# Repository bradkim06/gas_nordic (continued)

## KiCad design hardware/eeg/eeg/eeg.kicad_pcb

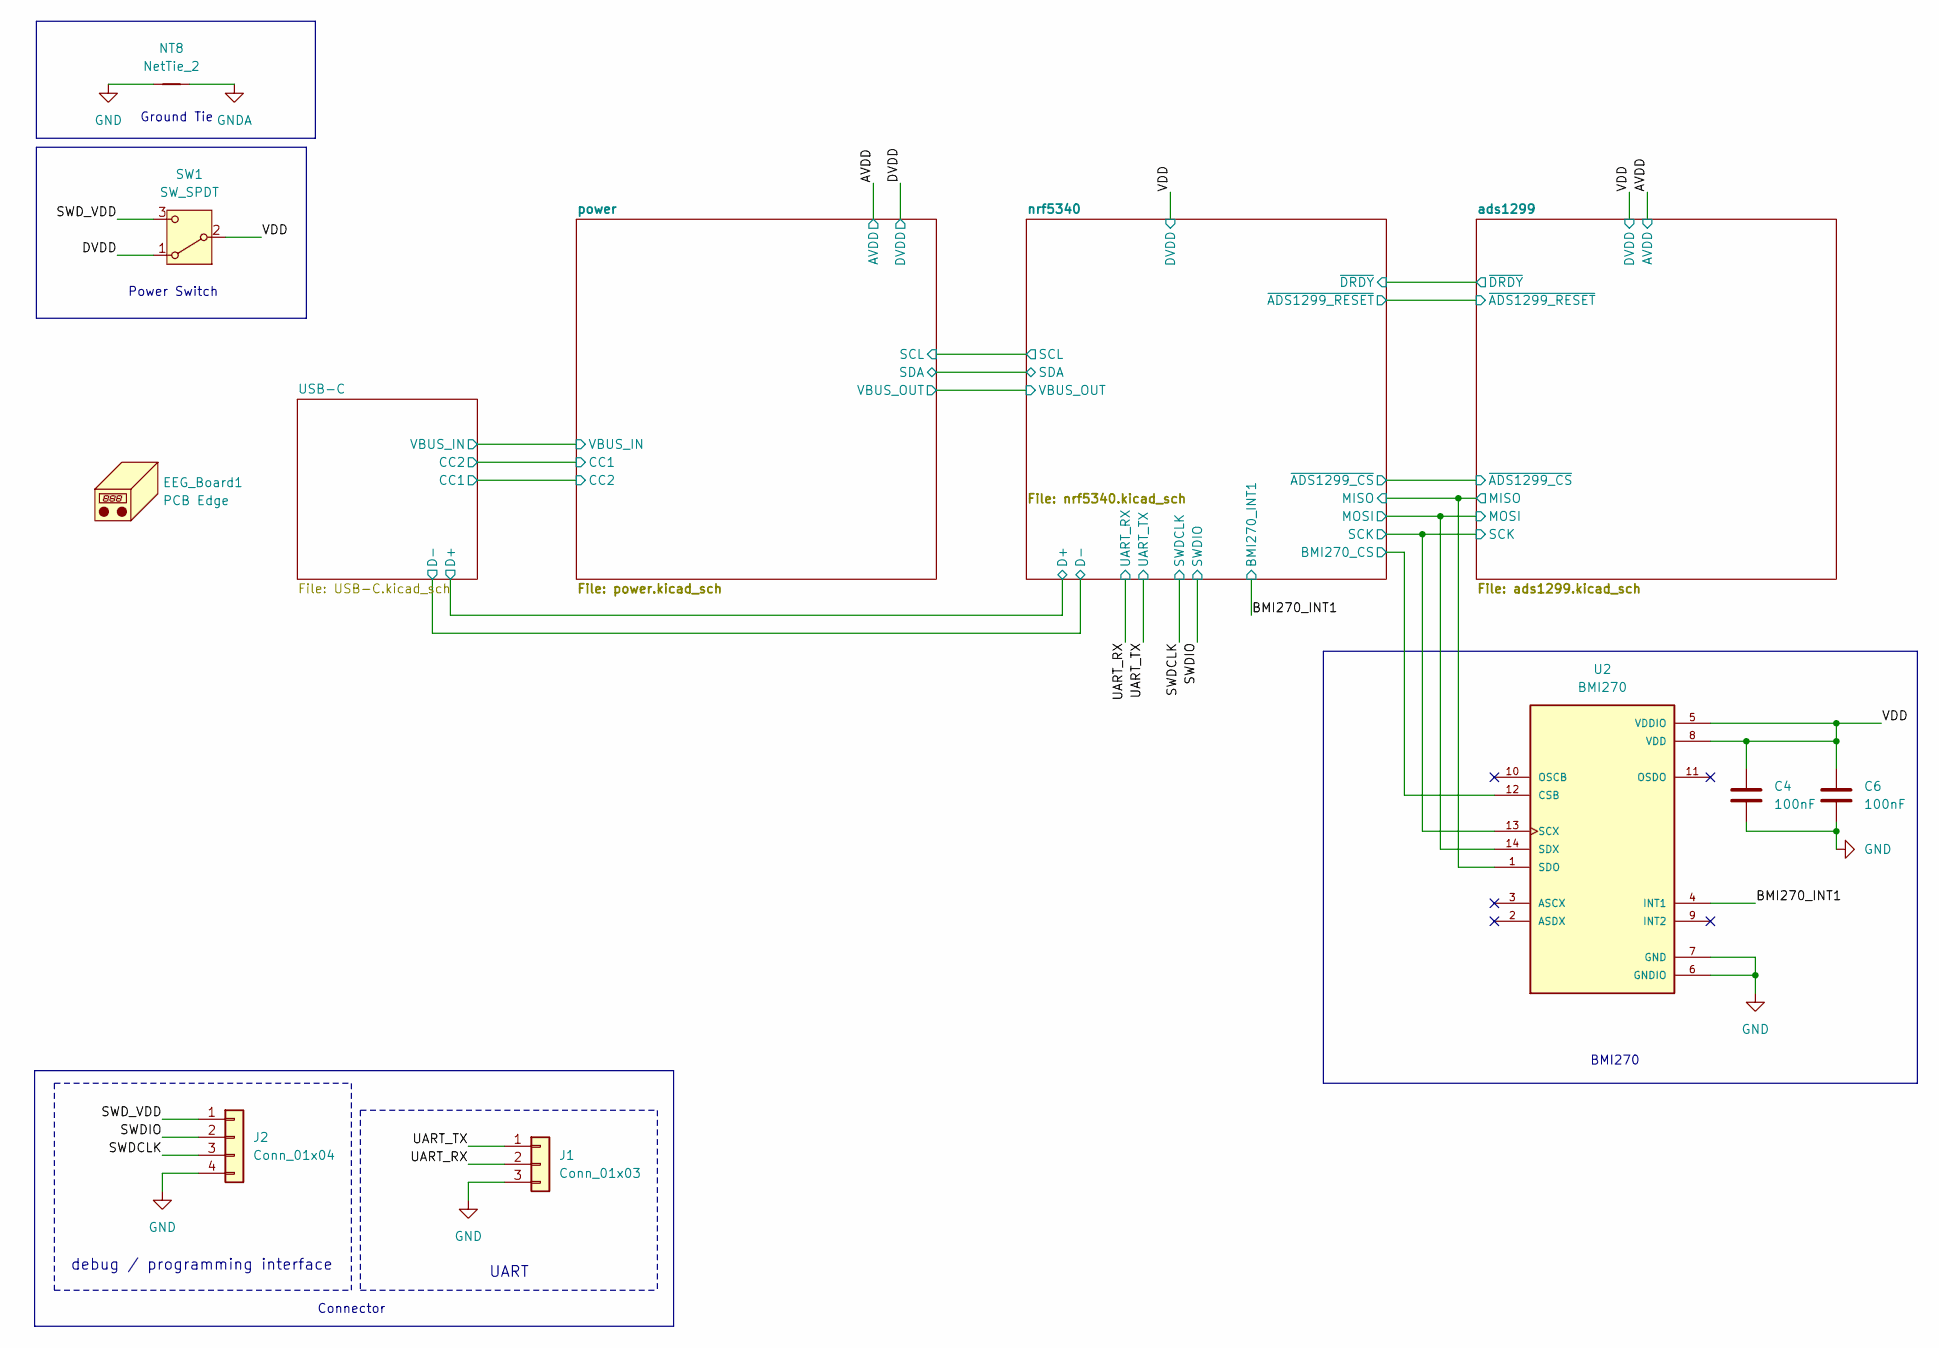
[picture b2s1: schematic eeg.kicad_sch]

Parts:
C4, C6: 100nF; C_0402_1005Metric; MANUFACTURER_PART_NUMBER GRM155R71C104KA88D
EEG_Board1: PCB Edge; eeg
J1: Conn_01x03; PinHeader_1x03_P1.27mm_Vertical; MANUFACTURER_PART_NUMBER 1.25T-3A
J2: Conn_01x04; PinHeader_1x04_P1.27mm_Vertical; MANUFACTURER_PART_NUMBER 1.25T-4A
NT8: NetTie_2; NetTie-2_SMD_Pad0.5mm
SW1: SW_SPDT; SK12D07VG4NSPA_CNK; MANUFACTURER_PART_NUMBER SK12D07VG5
U2: BMI270; XDCR_BMI270; MANUFACTURER_PART_NUMBER BMI270

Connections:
/BMI270_INT1: U2.4 (INT1); also elsewhere on the board
/DVDD: SW1.1 (A); also elsewhere on the board
/SWDCLK: J2.3; also elsewhere on the board
/SWDIO: J2.2; also elsewhere on the board
/SWD_VDD: J2.1, SW1.3 (C)
/UART_RX: J1.2; also elsewhere on the board
/UART_TX: J1.1; also elsewhere on the board
/VDD: C4.1, C6.1, SW1.2 (B), U2.5 (VDDIO), U2.8 (VDD); also elsewhere on the board
/ads1299/MISO: U2.1 (SDO); also elsewhere on the board
/ads1299/MOSI: U2.14 (SDX); also elsewhere on the board
/ads1299/SCK: U2.13 (SCX); also elsewhere on the board
/nrf5340/BMI270_CS: U2.12 (CSB); also elsewhere on the board
GND: C4.2, C6.2, J1.3, J2.4, NT8.1, U2.6 (GNDIO), U2.7 (GND); also elsewhere on the board
GNDA: NT8.2; also elsewhere on the board

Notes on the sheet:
Ground Tie
UART
Connector
BMI270
Power Switch
debug / programming interface

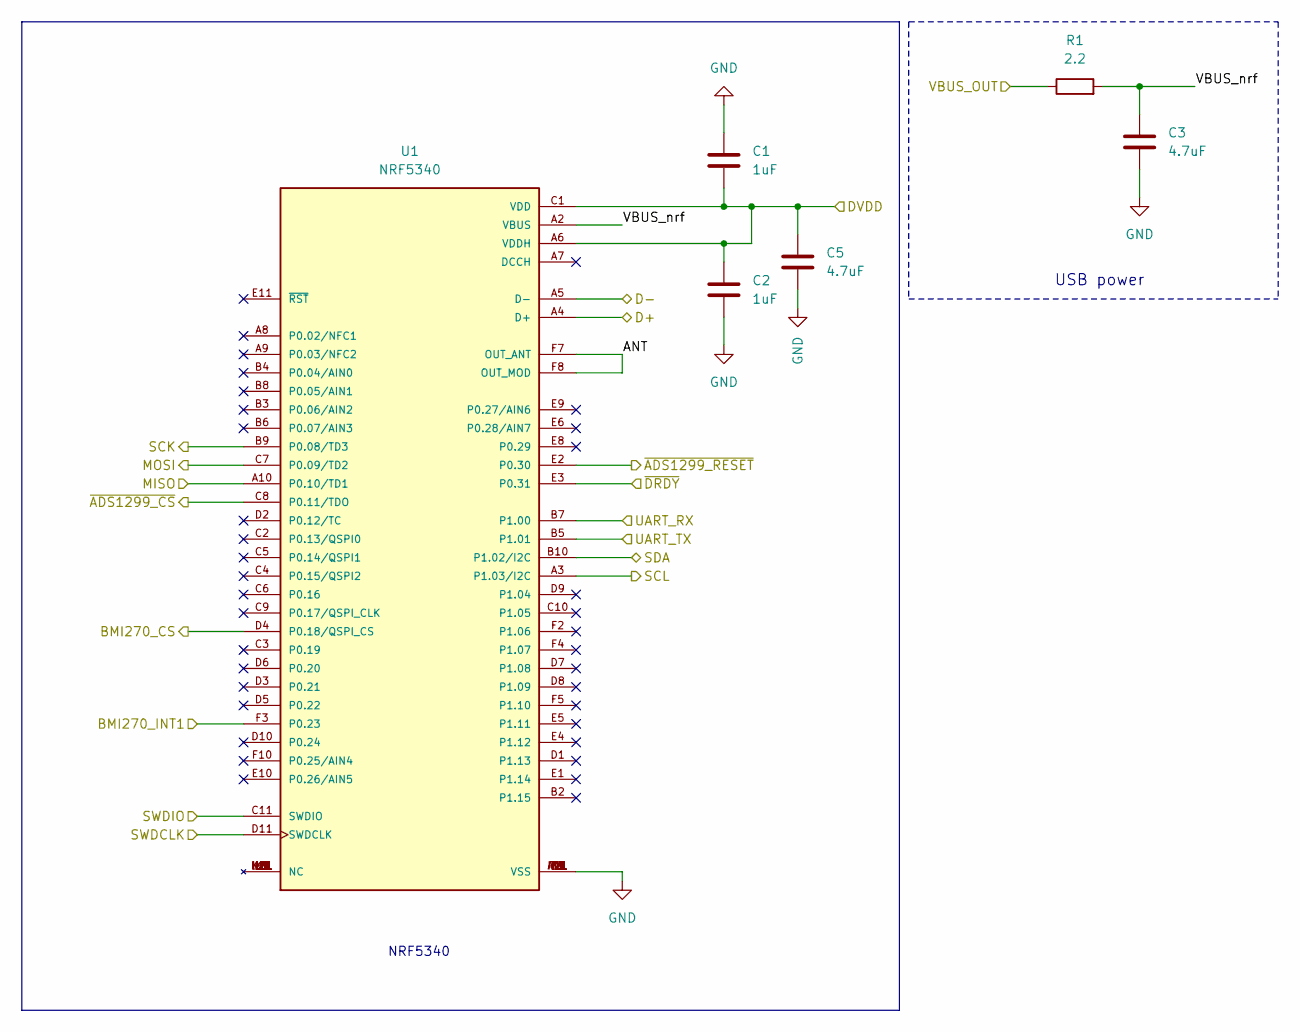
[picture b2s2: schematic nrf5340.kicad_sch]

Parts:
C1, C2: 1uF; C_0402_1005Metric; MANUFACTURER_PART_NUMBER GRM155R61A105KE15D
C3, C5: 4.7uF; C_0402_1005Metric; MANUFACTURER_PART_NUMBER GRM155R61A475MEAAD
R1: 2.2; R_0402_1005Metric; MANUFACTURER_PART_NUMBER RC0402FR-072R2L
U1: NRF5340; XCVR_ISP2053-AX-RS; PARTREV R6

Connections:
/BMI270_INT1: U1.F3 (P0.23); also elsewhere on the board
/SWDCLK: U1.D11 (SWDCLK); also elsewhere on the board
/SWDIO: U1.C11 (SWDIO); also elsewhere on the board
/UART_RX: U1.B7 (P1.00); also elsewhere on the board
/UART_TX: U1.B5 (P1.01); also elsewhere on the board
/USB-C/D+: U1.A4 (D+); also elsewhere on the board
/USB-C/D-: U1.A5 (D-); also elsewhere on the board
/VDD: C1.2, C2.1, C5.1, U1.A6 (VDDH), U1.C1 (VDD); also elsewhere on the board
/ads1299/MISO: U1.A10 (P0.10/TD1); also elsewhere on the board
/ads1299/MOSI: U1.C7 (P0.09/TD2); also elsewhere on the board
/ads1299/SCK: U1.B9 (P0.08/TD3); also elsewhere on the board
/ads1299/~ADS1299_CS: U1.C8 (P0.11/TDO); also elsewhere on the board
/ads1299/~ADS1299_RESET: U1.E2 (P0.30); also elsewhere on the board
/ads1299/~DRDY: U1.E3 (P0.31); also elsewhere on the board
/nrf5340/ANT: U1.F7 (OUT_ANT), U1.F8 (OUT_MOD)
/nrf5340/BMI270_CS: U1.D4 (P0.18/QSPI_CS); also elsewhere on the board
/nrf5340/SCL: U1.A3 (P1.03/I2C); also elsewhere on the board
/nrf5340/SDA: U1.B10 (P1.02/I2C); also elsewhere on the board
/nrf5340/VBUS_OUT: R1.1; also elsewhere on the board
/nrf5340/VBUS_nrf: C3.1, R1.2, U1.A2 (VBUS)
GND: C1.1, C2.2, C3.2, C5.2, U1.A1 (VSS), U1.A11 (VSS), U1.E7 (VSS), U1.F1 (VSS), U1.F6 (VSS), U1.F9 (VSS), U1.F11 (VSS); also elsewhere on the board

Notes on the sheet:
NRF5340
USB power

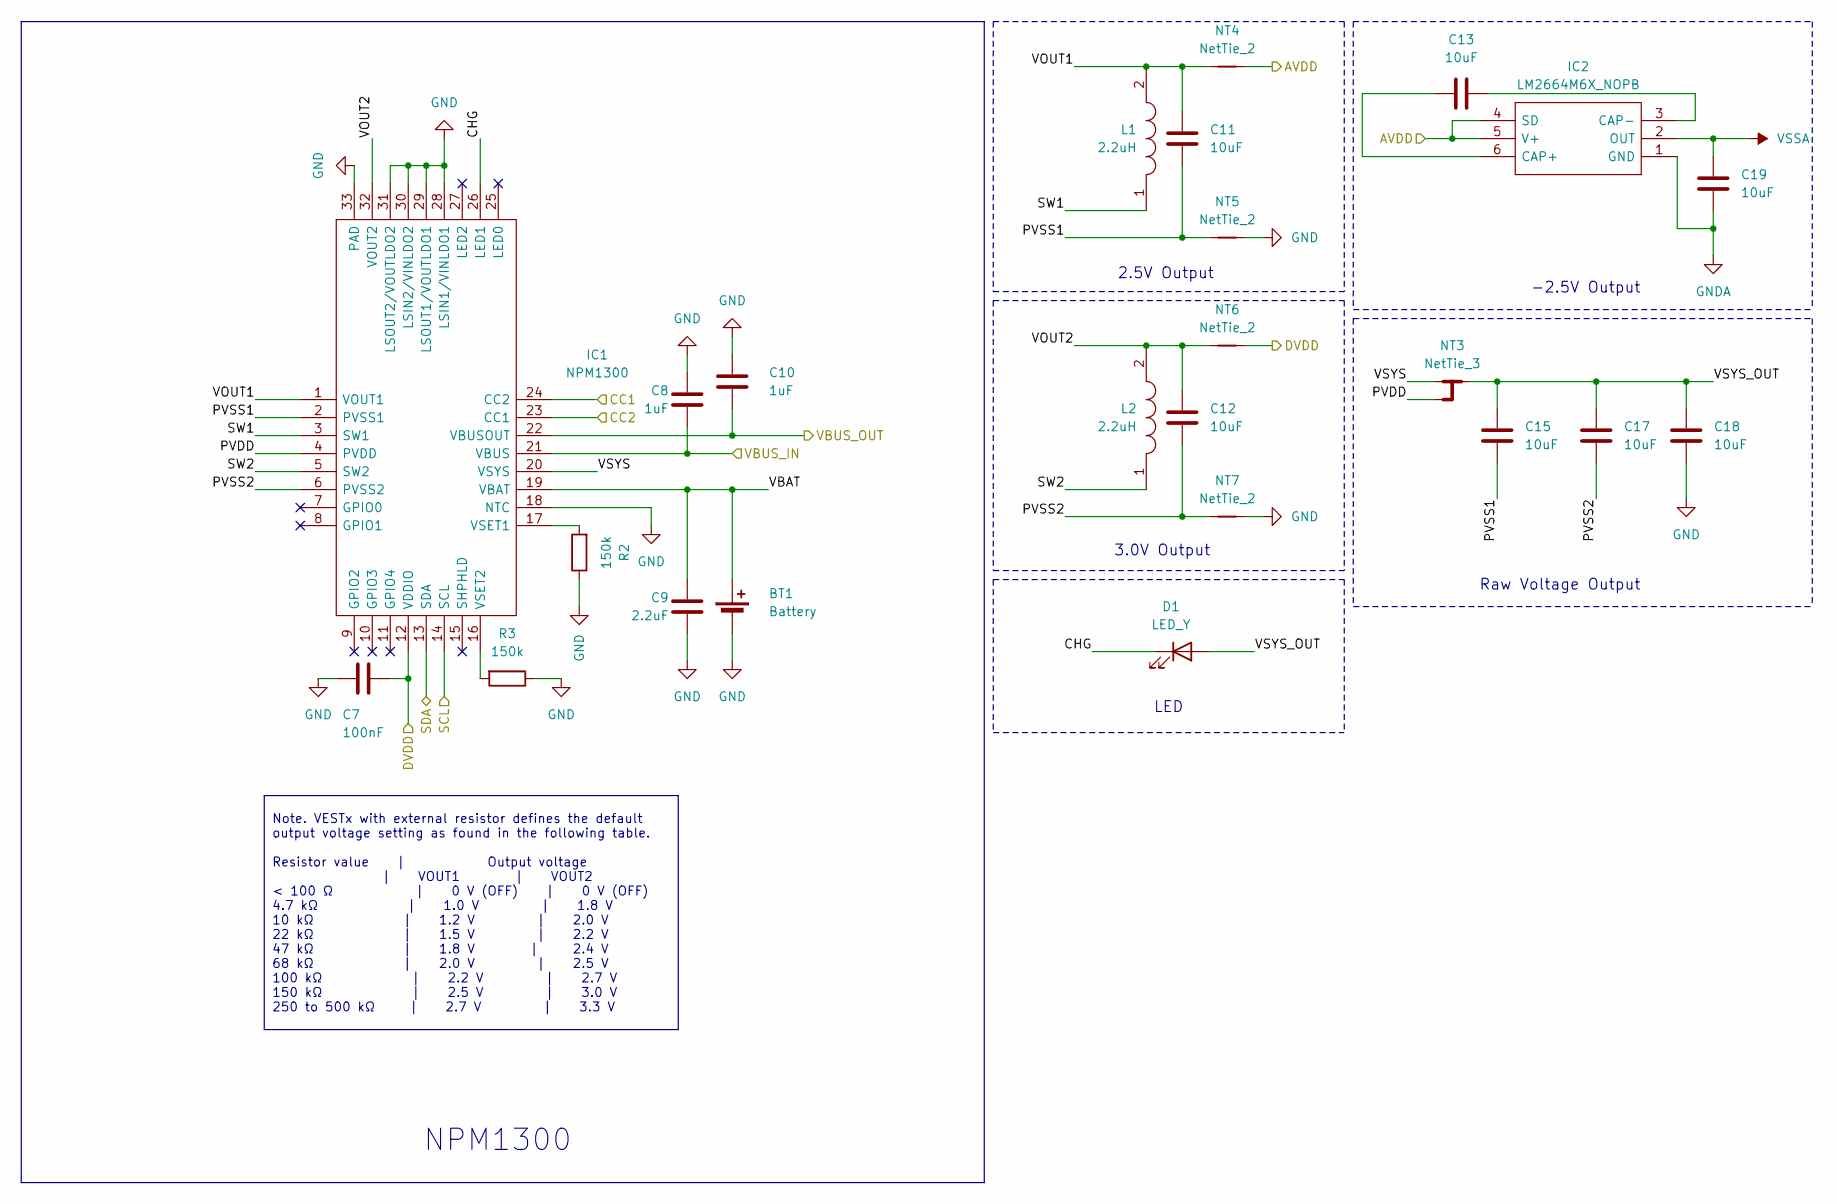
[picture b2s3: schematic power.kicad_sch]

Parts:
BT1: Battery; PinHeader_1x02_P1.27mm_Vertical; MANUFACTURER_PART_NUMBER 1.25T-2A
C7: 100nF; C_0402_1005Metric; MANUFACTURER_PART_NUMBER GRM155R71C104KA88D
C8, C10: 1uF; C_0402_1005Metric; MANUFACTURER_PART_NUMBER GRM155R61A105KE15D
C9: 2.2uF; C_0402_1005Metric; MANUFACTURER_PART_NUMBER GRM155Z71A225KE01D
C11, C12, C13, C15, C17, C18, C19: 10uF; C_0402_1005Metric; MANUFACTURER_PART_NUMBER GRM155R61A106ME44D
D1: LED_Y; LED_0603_1608Metric; MANUFACTURER_PART_NUMBER 19-213/Y2C-CQ2R2L/3T(CY)
IC1: NPM1300; QFN50P500X500X90-33N; Manufacturer_Part_Number NPM1300-QEAA-R; Mouser Part Number 949-NPM1300-QEAA-R
IC2: LM2664M6X_NOPB; SOT95P280X145-6N; Manufacturer_Part_Number LM2664M6X/NOPB; Mouser Part Number 926-LM2664M6X/NOPB
L1, L2: 2.2uH; INDC2016X100N; Manufacturer_Part_Number MLP2016H2R2MT0S1; Mouser Part Number 810-MLP2016H2R2MT0S1
NT3: NetTie_3; NetTie-3_SMD_Pad0.5mm
NT4, NT5, NT6, NT7: NetTie_2; NetTie-2_SMD_Pad0.5mm
R2, R3: 150k; R_0402_1005Metric; MANUFACTURER_PART_NUMBER RC0402FR-07150KL

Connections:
/AVDD: IC2.4 (SD), IC2.5 (V+), NT4.2; also elsewhere on the board
/DVDD: C7.1, IC1.12 (VDDIO), NT6.2; also elsewhere on the board
/USB-C/CC1: IC1.23 (CC1); also elsewhere on the board
/USB-C/CC2: IC1.24 (CC2); also elsewhere on the board
/USB-C/VBUS_IN: C8.1, IC1.21 (VBUS); also elsewhere on the board
/nrf5340/SCL: IC1.14 (SCL); also elsewhere on the board
/nrf5340/SDA: IC1.13 (SDA); also elsewhere on the board
/nrf5340/VBUS_OUT: C10.1, IC1.22 (VBUSOUT); also elsewhere on the board
/power/CHG: D1.1 (K), IC1.26 (LED1)
/power/PVDD: IC1.4 (PVDD), NT3.3
/power/PVSS1: C11.1, C15.1, IC1.2 (PVSS1), NT5.1
/power/PVSS2: C12.1, C17.1, IC1.6 (PVSS2), NT7.1
/power/SW1: IC1.3 (SW1), L1.1
/power/SW2: IC1.5 (SW2), L2.1
/power/VBAT: BT1.1 (+), C9.2, IC1.19 (VBAT)
/power/VOUT1: C11.2, IC1.1 (VOUT1), L1.2, NT4.1
/power/VOUT2: C12.2, IC1.32 (VOUT2), L2.2, NT6.1
/power/VSYS: IC1.20 (VSYS), NT3.1
/power/VSYS_OUT: C15.2, C17.2, C18.2, D1.2 (A), NT3.2
GND: BT1.2 (-), C7.2, C8.2, C9.1, C10.2, C18.1, IC1.18 (NTC), IC1.28 (LSIN1/VINLDO1), IC1.29 (LSOUT1/VOUTLDO1), IC1.30 (LSIN2/VINLDO2), IC1.31 (LSOUT2/VOUTLDO2), IC1.33 (PAD), NT5.2, NT7.2, R2.1, R3.1; also elsewhere on the board
GNDA: C19.1, IC2.1 (GND); also elsewhere on the board
unnamed: IC1.17 (VSET1), R2.2
unnamed: IC1.16 (VSET2), R3.2
unnamed: C13.1, IC2.6 (CAP+)
unnamed: C13.2, IC2.3 (CAP-)
VSSA: C19.2, IC2.2 (OUT); also elsewhere on the board

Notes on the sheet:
Note. VESTx with external resistor defines the default output voltage setting as found in the following table. Resistor value | Output voltage | VOUT1 | VOUT2 < 100 Ω | 0 V (OFF) | 0 V (OFF) 4.7 kΩ | 1.0 V | 1.8 V 10 kΩ | 1.2 V | 2.0 V 22 kΩ | 1.5 V | 2.2 V 47 kΩ | 1.8 V | 2.4 V 68 kΩ | 2.0 V | 2.5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
-2.5V Output
Raw Voltage Output
3.0V Output
2.5V Output
LED
NPM1300

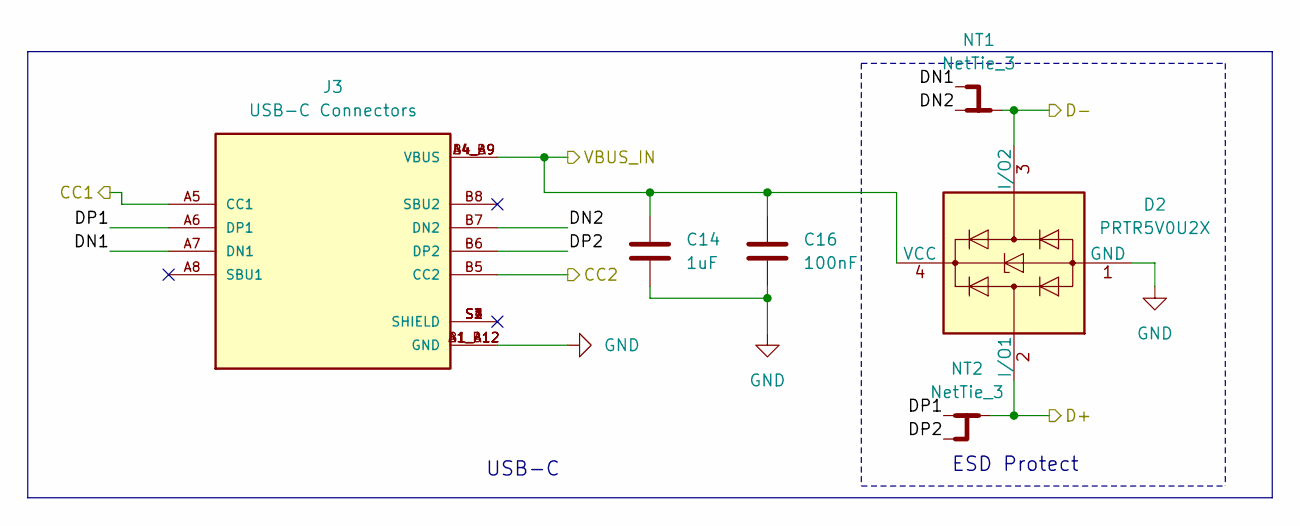
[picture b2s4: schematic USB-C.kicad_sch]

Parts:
C14: 1uF; C_0402_1005Metric; MANUFACTURER_PART_NUMBER GRM155R61A105KE15D
C16: 100nF; C_0402_1005Metric; MANUFACTURER_PART_NUMBER GRM155R71C104KA88D
D2: PRTR5V0U2X; SOT-143; MANUFACTURER_PART_NUMBER PRTR5V0U2X,215
J3: USB-C Connectors; HRO_TYPE-C-31-M-12; PARTREV 2020.12.08
NT1, NT2: NetTie_3; NetTie-3_SMD_Pad0.5mm

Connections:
/USB-C/CC1: J3.A5 (CC1); also elsewhere on the board
/USB-C/CC2: J3.B5 (CC2); also elsewhere on the board
/USB-C/D+: D2.2 (I/O1), NT2.2; also elsewhere on the board
/USB-C/D-: D2.3 (I/O2), NT1.2; also elsewhere on the board
/USB-C/DN1: J3.A7 (DN1), NT1.3
/USB-C/DN2: J3.B7 (DN2), NT1.1
/USB-C/DP1: J3.A6 (DP1), NT2.1
/USB-C/DP2: J3.B6 (DP2), NT2.3
/USB-C/VBUS_IN: C14.2, C16.2, D2.4 (VCC), J3.A4_B9 (VBUS), J3.B4_A9 (VBUS); also elsewhere on the board
GND: C14.1, C16.1, D2.1 (GND), J3.A1_B12 (GND), J3.B1_A12 (GND); also elsewhere on the board

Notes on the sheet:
ESD Protect
USB-C

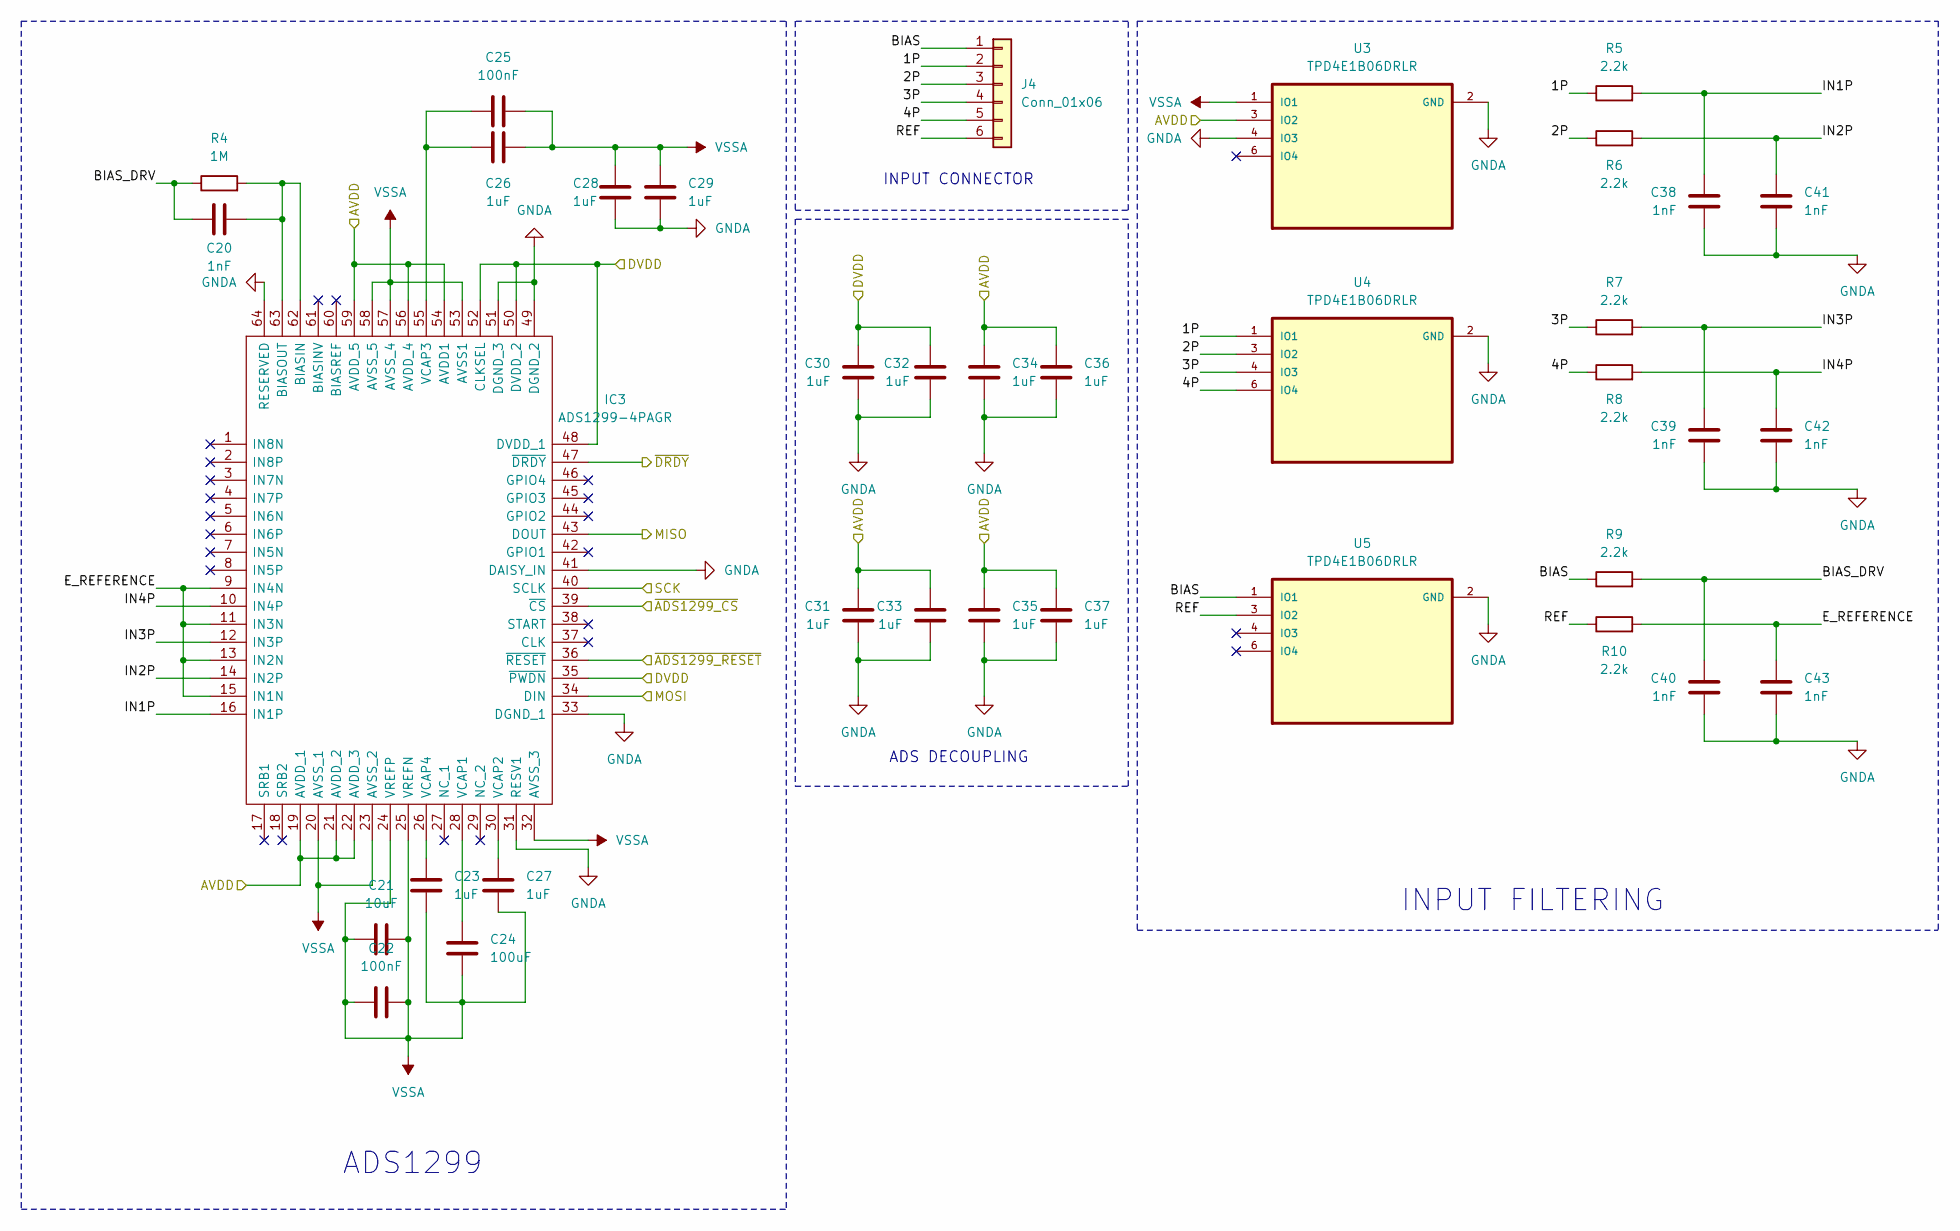
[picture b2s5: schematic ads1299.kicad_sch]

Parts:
C20, C38, C39, C40, C41, C42, C43: 1nF; C_0402_1005Metric; MANUFACTURER_PART_NUMBER GRM155R71H102KA01D
C21: 10uF; C_0402_1005Metric; MANUFACTURER_PART_NUMBER GRM155R61A106ME44D
C22, C25: 100nF; C_0402_1005Metric; MANUFACTURER_PART_NUMBER GRM155R71C104KA88D
C23, C26, C27, C28, C29, C30, C31, C32, C33, C34, C35, C36, C37: 1uF; C_0402_1005Metric; MANUFACTURER_PART_NUMBER GRM155R61A105KE15D
C24: 100uF; C_0402_1005Metric; MANUFACTURER_PART_NUMBER GRM21BR60J107ME15L
IC3: ADS1299-4PAGR; QFP50P1200X1200X120-64N; Manufacturer_Part_Number ADS1299-4PAGR; Mouser Part Number 595-ADS1299-4PAGR
J4: Conn_01x06; PinHeader_1x06_P1.27mm_Vertical; MANUFACTURER_PART_NUMBER 1.25T-6A
R4: 1M; R_0402_1005Metric; MANUFACTURER_PART_NUMBER RC0402FR-071ML
R5, R6, R7, R8, R9, R10: 2.2k; R_0402_1005Metric; MANUFACTURER_PART_NUMBER RC0402FR-071ML
U3, U4, U5: TPD4E1B06DRLR; SOT50P160X60-6N; MANUFACTURER_PART_NUMBER TPD4E1B06DRLR

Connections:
/AVDD: C31.2, C33.2, C34.2, C35.2, C36.2, C37.2, IC3.19 (AVDD_1), IC3.21 (AVDD_2), IC3.22 (AVDD_3), IC3.54 (AVDD1), IC3.56 (AVDD_4), IC3.59 (AVDD_5), U3.3 (IO2); also elsewhere on the board
/VDD: C30.2, C32.2, IC3.35 (~PWDN), IC3.48 (DVDD_1), IC3.50 (DVDD_2), IC3.52 (CLKSEL); also elsewhere on the board
/ads1299/1P: J4.2, R5.1, U4.1 (IO1)
/ads1299/2P: J4.3, R6.1, U4.3 (IO2)
/ads1299/3P: J4.4, R7.1, U4.4 (IO3)
/ads1299/4P: J4.5, R8.1, U4.6 (IO4)
/ads1299/BIAS: J4.1, R9.1, U5.1 (IO1)
/ads1299/BIAS_DRV: C20.1, C40.2, R4.1, R9.2
/ads1299/E_REFERENCE: C43.2, IC3.9 (IN4N), IC3.11 (IN3N), IC3.13 (IN2N), IC3.15 (IN1N), R10.2
/ads1299/IN1P: C38.2, IC3.16 (IN1P), R5.2
/ads1299/IN2P: C41.2, IC3.14 (IN2P), R6.2
/ads1299/IN3P: C39.2, IC3.12 (IN3P), R7.2
/ads1299/IN4P: C42.2, IC3.10 (IN4P), R8.2
/ads1299/MISO: IC3.43 (DOUT); also elsewhere on the board
/ads1299/MOSI: IC3.34 (DIN); also elsewhere on the board
/ads1299/REF: J4.6, R10.1, U5.3 (IO2)
/ads1299/SCK: IC3.40 (SCLK); also elsewhere on the board
/ads1299/~ADS1299_CS: IC3.39 (~CS); also elsewhere on the board
/ads1299/~ADS1299_RESET: IC3.36 (~RESET); also elsewhere on the board
/ads1299/~DRDY: IC3.47 (~DRDY); also elsewhere on the board
GNDA: C28.1, C29.1, C30.1, C31.1, C32.1, C33.1, C34.1, C35.1, C36.1, C37.1, C38.1, C39.1, C40.1, C41.1, C42.1, C43.1, IC3.31 (RESV1), IC3.33 (DGND_1), IC3.41 (DAISY_IN), IC3.49 (DGND_2), IC3.51 (DGND_3), IC3.64 (RESERVED), U3.2 (GND), U3.4 (IO3), U4.2 (GND), U5.2 (GND); also elsewhere on the board
unnamed: C20.2, IC3.62 (BIASIN), IC3.63 (BIASOUT), R4.2
unnamed: C24.1, IC3.28 (VCAP1)
unnamed: C27.1, IC3.30 (VCAP2)
unnamed: C25.1, C26.1, IC3.55 (VCAP3)
unnamed: C23.1, IC3.26 (VCAP4)
VSSA: C21.1, C21.2, C22.1, C22.2, C23.2, C24.2, C25.2, C26.2, C27.2, C28.2, C29.2, IC3.20 (AVSS_1), IC3.23 (AVSS_2), IC3.24 (VREFP), IC3.25 (VREFN), IC3.32 (AVSS_3), IC3.53 (AVSS1), IC3.57 (AVSS_4), IC3.58 (AVSS_5), U3.1 (IO1); also elsewhere on the board

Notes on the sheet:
ADS DECOUPLING
ADS1299
INPUT CONNECTOR
INPUT FILTERING

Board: 6 copper layers, 80 parts (0 on the bottom side), 65 nets, no tracks yet.

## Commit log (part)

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2023-09-13 Feat:Log: 모듈 추가
2023-09-13 Doc: sample.yaml delete
2023-09-13 Fix:Kconfig: log config add
2023-09-13 Fix:battery: batt_mon.c & battery.h integrate to battery.c
2023-09-13 Fix:load_switch: switch 코드 파일 분할 & SYS_INIT
2023-09-13 Feat:battery: low battery indicator led ctrl
2023-09-13 Fix:bme680: result data struct add
2023-09-14 Fix:Log: dbg -> inf
2023-09-19 Feat:ble: ble create
2023-09-20 Fix:Log: delete line break
2023-09-20 Fix:dts: load_switch (dts -> overlay)
2023-09-20 Fix: Refactoring code
2023-09-22 Doc: README
2023-10-05 Feat: PCBA test ok
2023-10-06 Feat: bme680 sensor test ok
    - load switch gpio hogging
2023-10-13 Feat: Board Out of Tree
2023-10-13 Style: clang-foramt run
2023-10-16 Fix: bme68x gas disable
2023-10-17 Fix: Low Power Consumption Setting
2023-10-17 Fix: App Log Module Fix
2023-10-18 Fix: bme680 result ble tx & BLE MTU data length default -> max
2023-10-18 Feat: Time Stamp add
2023-10-18 Style: clang-foramt
2023-10-20 Fix: Bluetooth mtu sync bug fix
2023-10-20 Fix: bme680 Fractional value presicion fix
2023-10-24 Doc: Update Schematic File
2023-10-24 Fix: Debug prj option, cmake flash runner add
2023-10-25 Fix: bme680 classfication code & doc update
2023-10-25 Feat: License add
2023-10-25 Doc: readme update
2023-10-26 Doc: Correction of the typo in the 'VOC table' poor ppm range
2023-10-26 cmake: release.conf fix
2023-10-26 gas: increase measure period
2023-10-26 dts: Update GPIO pin settings to match hardware rev 1.0.0
2023-10-26 ble: Extend the supervision timeout from 12 seconds to 16 seconds due to a connection loss
2023-10-26 batt: tw-403030 batt max value add
2023-10-27 adc: increase sample size
2023-10-31 ble: Add data passing semaphore
2023-10-31 style: refactor code
2023-11-01 cmake: fix extra modules list -> set
2023-11-01 driver: bme680 library git exclude & path fix
2023-11-02 format: format.sh fix
2023-11-03 refactor: free_moving_average() fix
    Changes made:
    1. Changed the function parameter to a pointer to a pointer. This allows us to set the pointer to NULL in the calling function, preventing dangling pointers.
    2. Added a NULL check for the function parameter to prevent dereferencing NULL pointers.
    3. Improved the variable name from `av_obj` to `avg_obj` for clarity.
    4. Added a Doxygen style comment to describe the function.
2023-11-03 refactor: bug fix
2023-11-03 Doc: calculate_level_pptt comment ad
2023-11-03 refactor: gas code
2023-11-03 Refactor: Improve code readability and consistency
    This commit includes several changes aimed at improving code readability
    and consistency across multiple files. The changes include:
    - Renamed `batt_value` to `battery_value` for clarity.
    - Renamed `notify_gas_enabled` to `bt_notify_enable` for consistency.
    - Renamed `bt_thread_fn` to `bluetooth_thread` for clarity.
    - Renamed `fw_info` to `firmware_info` for clarity.
2023-11-06 Bluetooth: Refactor gas sensor data notification function
    This commit refactors the function that sends gas sensor data via Bluetooth notification. The changes include:
    - Renaming the function parameter to make it clear that it's a pointer to the gas sensor data.
    - Changing the log string to include the length of the data being sent.
    - Updating the warning log message to use more standard language ("smaller than" instead of "small than").
    - Changing the return statement to cast the data length to size_t.
    In addition, a minor change was made in the bme680_app.c file to change an error log message to a warning, as the condition being logged is a possible case.
2023-11-06 bme680: Refactor code for clarity and strictness
    This commit includes several changes to improve code clarity and
    strictness.
    - In .clangd, the Diagnostics section has been updated to enforce
    strict checking of unused includes.
    - In bme680_app.c, the inclusion of "bluetooth.h" is now conditional
    based on the CONFIG_BME68X_IAQ_EN flag.
2023-11-06 gas: Simplify millivolts calculation in convert_adc_to_mv
    This commit simplifies the calculation of millivolts in the
    convert_adc_to_mv function. The previous if-else structure is replaced
    with a ternary operator, reducing the number of lines and improving
    readability.
2023-11-06 CMake: Refactor for readability and consistency
    This commit refactors the CMakeLists.txt files for improved readability and consistency. Changes include:
    - Switching from uppercase to lowercase for function names, in line with CMake best practices.
    - Adding line breaks and indentation for better readability in complex function calls.
    - Reformatting comments for consistency and clarity.
    No functional changes are introduced with this commit.
2023-11-07 Refactor: Add end of line comments for preprocessor directives
    This commit enhances the readability of the code by adding end of line comments to each `#endif` preprocessor directive in the source files.
2023-11-08 thread: Adjust thread priorities in various subsystems
    This commit adjusts the thread priorities for the following subsystems: battery, bluetooth, bme680, gas, and led.
    The aim is to optimize performance by adjusting the thread priorities to better suit the workload and importance of each subsystem.
    The new priority levels are as follows:
    - Battery: 3
    - Bluetooth: 0
    - BME680: 1
2023-11-08 battery: Adjust lower voltage threshold from 3100 to 3000
2023-11-21 Symbolic link compile_commands.json for better IDE integration
2023-11-21 Commit: Fixed markdown formatting issues in README.md
    This commit addresses some markdown formatting issues in the README.md file. The changes include escaping special characters to ensure they are correctly displayed.
2023-11-21 Refactor: Minor code clean up and comment updates
    This commit includes a few minor changes to improve code readability and maintainability. The changes include:
    - Reordered the include statements in bme68x_iaq.c for better organization.
    - Fixed a typo in a comment in battery.c.
    - Removed an unnecessary return comment in bme680_app.c.
    - Added specific developer TODO tags in gas.c for better tracking of tasks.
    - Added a developer tag to a TODO comment for handling temperature sensor error case in gas.c.
2023-11-21 Adjust battery and gas measurement parameters for improved performance
    This commit modifies several parameters related to battery and gas measurement.
    In battery.c, the battery level point has been adjusted from 3550 to 3300 for better battery performance. The log message formatting has been changed to use snprintf instead of sprintf for safer stri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
    In gas.c, the gas average filter size has been reduced from 30 to 10 for faster calculation.
    These changes aim to improve the performance and efficiency of th
2023-11-22 doc: Update CPPLINT configuration and TODO comments in gas.c and gas.h
    The CPPLINT.cfg file has been updated to include '-readability/todo' in the filter.
    In addition, the TODO comments in gas.c and gas.h have been modified to remove specific usernames. The comments now just read 'TODO:' followed by the task description. This change is in line with bes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
2023-11-28 refactor:bluetooth: Fix buffer sizes and snprintf usage
    This patch fixes several issues related to buffer sizes and the use of sprintf in bluetooth.c. It ensures that buffers are correctly sized to include the null-terminator and replaces sprintf with snp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
2023-11-28 battery: Improve dynamic log message allocation in battery status check
    The existing static allocation for log messages in measure_battery_status() could potentially lead to buffer overflows if the formatted string exceeds the size of MAX_LOG_CASE. This commit replaces t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
2023-12-06 bluetooth: Correct notification data format string in bluetooth_thread
    This patch removes the extraneous 'u' from the format string
2023-12-06 gas: create code for H2S sensor
    This commit introduces several changes across Kconfig, device tree source, and the gas sensor implementation for the HHS NRF52832 board:
    - The device tree source file for the HHS NRF52832 board is updated with corrected ADC configuration values and pin assignments for gas monitoring channels.
    - The `src/gas.h` header file is updated with new measurement range and temperature coefficient data for H2S gas sensors.
2023-12-06 bluetooth: change message format for gas sensor in bluetooth_thread
    The message format string used for creating notification data in bluetooth_thread() was missing a placeholder for the fractional part of the gas sensor value. This commit corrects the format string t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
2023-12-08 CMake: Add debug configuration and refactor project settings
    This commit introduces a new debug configuration file and refactors the project settings. The debug.conf file has been simplified to only include necessary debug options, and the release.conf has bee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
2023-12-11 adc: Clean up sensor voltage calculation comments
    The comments in the device tree source and header file related to the sensor voltage calculations were inconsistent and contained outdated information. This commit cleans up the comments to reflect t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
2023-12-12 README: Add firmware flowchart for portable gas detector
    The README.md file has been updated to include a flowchart that outlines the firmware logic for a portable gas measuring device. The flowchart, created using the Mermaid syntax, details the initializ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
2023-12-12 Bluetooth: fix BT_DEVICE_NAME
    the device name to "HHS_G0001" to reflect the intended device identifier.
2023-12-13 bluetooth: Adjust TIMEOUT_SEC to 10 seconds
2023-12-13 build: cmake: Comment out debug.conf inclusion in CMakeLists
2023-12-13 gas: Remove unused coefficient calculation in calibration function
    The coefficient calculation in the calculate_calibrated_mv function was commented out as it was not being used in the final calculation. The return value now directly uses the raw millivolt value. Ad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
2024-01-08 feat: Adapted to match hardware version 1.0.1
2024-01-17 doc: hardware design add(kicad)
2024-01-23 led: re-enable thread definition, Adjust LED blink rate and brightness for power optimization
    This commit updates the LED blink rate and brightness to more suitable values. average current consumption is 5~10uA
2024-03-18 adc: acquisition time up
2024-03-18 Update CMakeLists.txt for HHS_nrf52832 board and BME68X_IAQ driver
    In this commit, the CMakeLists.txt files for the HHS_nrf52832 board and BME68X_IAQ driver are updated to reflect necessary changes.
    Changes in CMakeLists.txt for HHS_nrf52832 board:
    - Removed the setting of CONF_FILE variable.
    - Updated BOARD_ROOT to use ${CMAKE_SOURCE_DIR}.
    - Updated BOARD configuration to hhs_nrf52832.
    Changes in CMakeLists.txt for BME68X_IAQ driver:
2024-05-30 ble: 블루투스 온도 소수점 추가
2024-08-02 fix: temperature calibration restore
2024-09-12 feat: hw revision 1.0.2
    Rev 1.0.2
    - Oxygen Sensor
    - Voltage Amplification Ratio AdjustmentR18(10.7 -> 10k), R12(2.0k -> 2M)
    -> Reduce Current Consumption
    - Addition of lowpass filter for Noise Reduction
    - Gas Sensor
2024-10-15 feat: hw revision 1.0.3
2024-10-17 feat: add ble advertise name change
2024-10-23 test: kcl gas test
2024-11-14 test: kcl test ok
2025-03-27 feat: hw revision 2.0.1
2025-04-14 feat: periodic calibration
2025-06-09 Fix typos in VOC and CO2 tables
2025-06-09 Simplify CODE_IF_ELSE macro
2025-07-02 led on
2025-07-02 Add power switch and system power management
2025-09-03 restore hw 2.0.1
2025-09-25 docs: refresh firmware overview in README
2025-09-25 Update comments to reflect current behavior
